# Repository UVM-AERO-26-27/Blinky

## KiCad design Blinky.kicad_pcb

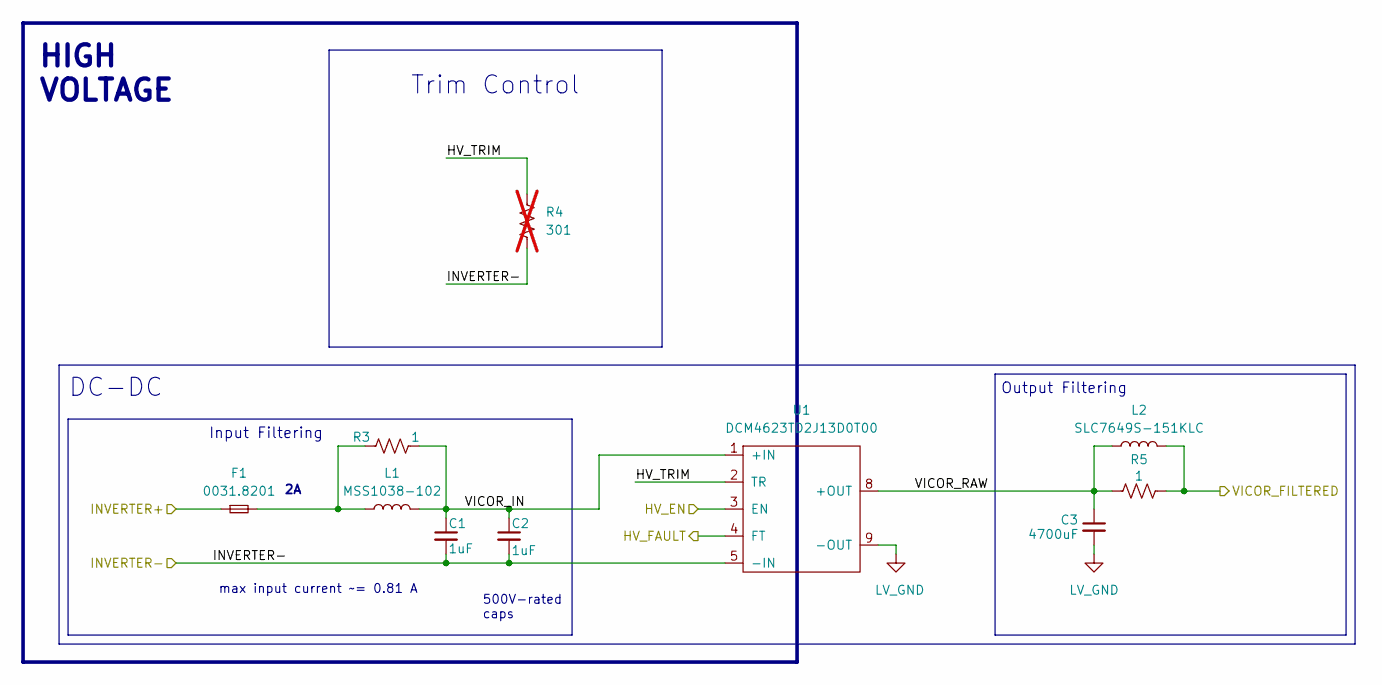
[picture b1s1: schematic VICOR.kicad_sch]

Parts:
C1, C2: 1uF; C_Rect_L18.0mm_W8.0mm_P15.00mm_FKS3_FKP3
C3: 4700uF; C_Radial_D12.5mm_H25.0mm_P5.00mm
F1: 0031.8201; Fuseholder_Cylinder-5x20mm_Schurter_0031_8201_Horizontal_Op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
L1: MSS1038-102
L2: SLC7649S-151KLC
R3, R5: 1; R_2512_6332Metric_Pad1.40x3.35mm_HandSolder; Manufacturer_Part_Number RK73H1JTTD1002F; Digikey part number 2019-RK73H1JTTD1002FCT-ND
R4: 301; R_0805_2012Metric_Pad1.20x1.40mm_HandSolder; not fitted
U1: DCM4623TD2J13D0T00

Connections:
/Control Signals/HV_EN: U1.3 (EN); also elsewhere on the board
/Control Signals/HV_FAULT: U1.4 (FT); also elsewhere on the board
/Control Signals/INVERTER-: C1.2, C2.2, R4.2, U1.5 (-IN); also elsewhere on the board
/GLV Connectors/VICOR_FILTERED: L2.2, R5.1; also elsewhere on the board
/TSV Connectors/INVERTER+: F1.1; also elsewhere on the board
/VICOR-1/HV_TRIM: R4.1, U1.2 (TR)
/VICOR-1/VICOR_IN: C1.1, C2.1, L1.2, R3.1, U1.1 (+IN)
/VICOR-1/VICOR_RAW: C3.1, L2.1, R5.2, U1.8 (+OUT)
LV_GND: C3.2, U1.9 (-OUT); also elsewhere on the board
unnamed: F1.2, L1.1, R3.2

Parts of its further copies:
C4, C5: 1uF; C_Rect_L18.0mm_W8.0mm_P15.00mm_FKS3_FKP3
C6: 4700uF; C_Radial_D12.5mm_H25.0mm_P5.00mm
L3: MSS1038-102
L4: SLC7649S-151KLC
R6, R8: 1; R_2512_6332Metric_Pad1.40x3.35mm_HandSolder; Manufacturer_Part_Number RK73H1JTTD1002F; Digikey part number 2019-RK73H1JTTD1002FCT-ND
R7: 301; R_0805_2012Metric_Pad1.20x1.40mm_HandSolder; not fitted
U2: DCM4623TD2J13D0T00

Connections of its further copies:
/Control Signals/HV_EN: U2.3 (EN); also elsewhere on the board
/Control Signals/HV_FAULT: U2.4 (FT); also elsewhere on the board
/Control Signals/INVERTER-: C4.2, C5.2, R7.2, U2.5 (-IN); also elsewhere on the board
/GLV Connectors/VICOR_FILTERED: L4.2, R8.1; also elsewhere on the board
/VICOR-2/HV_TRIM: R7.1, U2.2 (TR)
/VICOR-2/VICOR_IN: C4.1, C5.1, L3.2, R6.1, U2.1 (+IN)
/VICOR-2/VICOR_RAW: C6.1, L4.1, R8.2, U2.8 (+OUT)
LV_GND: C6.2, U2.9 (-OUT); also elsewhere on the board
unnamed 22: L3.1, R6.2; also elsewhere on the board

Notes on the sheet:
DC-DC
Input Filtering
Output Filtering
Trim Control
max input current ~= 0.81 A
HIGH VOLTAGE
500V-rated caps

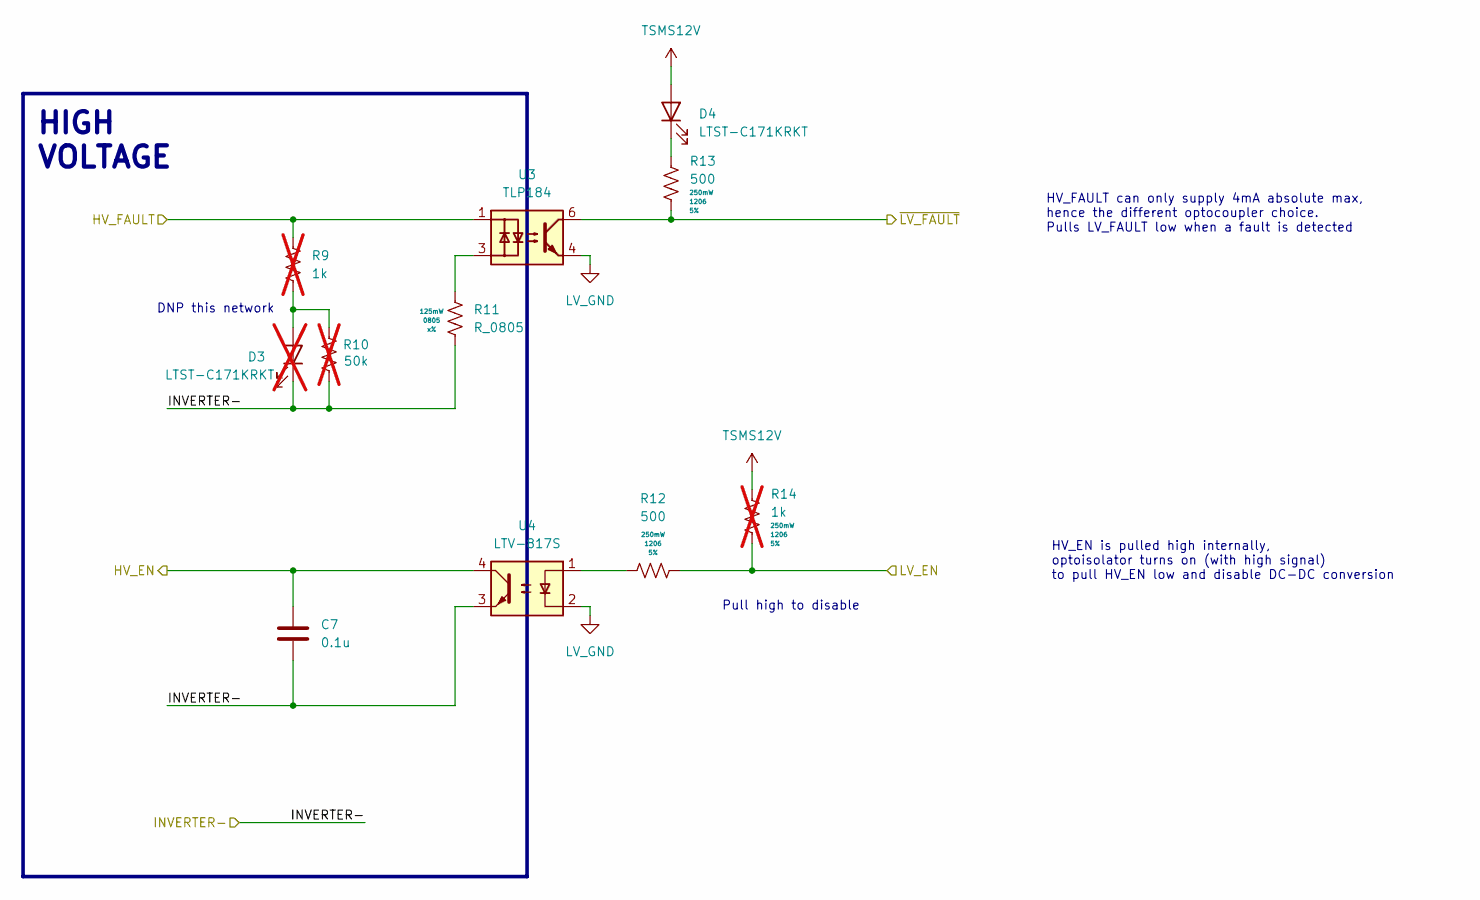
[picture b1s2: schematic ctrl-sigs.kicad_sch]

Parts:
C7: 0.1u; C_0603_1608Metric
D3: LTST-C171KRKT; LED_0805_2012Metric; not fitted
D4: LTST-C171KRKT; LED_0805_2012Metric
R9: 1k; R_0603_1608Metric_Pad0.98x0.95mm_HandSolder; not fitted
R10: 50k; R_0603_1608Metric_Pad0.98x0.95mm_HandSolder; Manufacturer_Part_Number RMCF0603FT1K00; Digikey part number RMCF0603FT1K00CT-ND; not fitted
R11: R_0805; R_0805_2012Metric_Pad1.20x1.40mm_HandSolder; Tolerance x%
R12, R13: 500; R_1206_3216Metric_Pad1.30x1.75mm_HandSolder; Tolerance 5%
R14: 1k; R_1206_3216Metric_Pad1.30x1.75mm_HandSolder; Tolerance 5%; not fitted
U3: TLP184; Toshiba_SOIC-4-6_4.4x3.6mm_P1.27mm
U4: LTV-817S; SMDIP-4_W9.53mm

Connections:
/Control Signals/HV_EN: C7.1, U4.4; also elsewhere on the board
/Control Signals/HV_FAULT: R9.1, U3.1; also elsewhere on the board
/Control Signals/INVERTER-: C7.2, D3.1 (K), R10.1, R11.2, U4.3; also elsewhere on the board
/Control Signals/LV_EN: R12.2, R14.1; also elsewhere on the board
/Control Signals/~LV_FAULT: R13.1, U3.6; also elsewhere on the board
LV_GND: U3.4, U4.2; also elsewhere on the board
unnamed: D3.2 (A), R9.2, R10.2
unnamed: D4.1 (K), R13.2
unnamed: R11.1, U3.3
unnamed: R12.1, U4.1
TSMS12V: D4.2 (A), R14.2; also elsewhere on the board

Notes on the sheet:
HV_FAULT can only supply 4mA absolute max, hence the different optocoupler choice. Pulls LV_FAULT low when a fault is detected
DNP this network
HV_EN is pulled high internally, optoisolator turns on (with high signal) to pull HV_EN low and disable DC-DC conversion
Pull high to disable
HIGH VOLTAGE

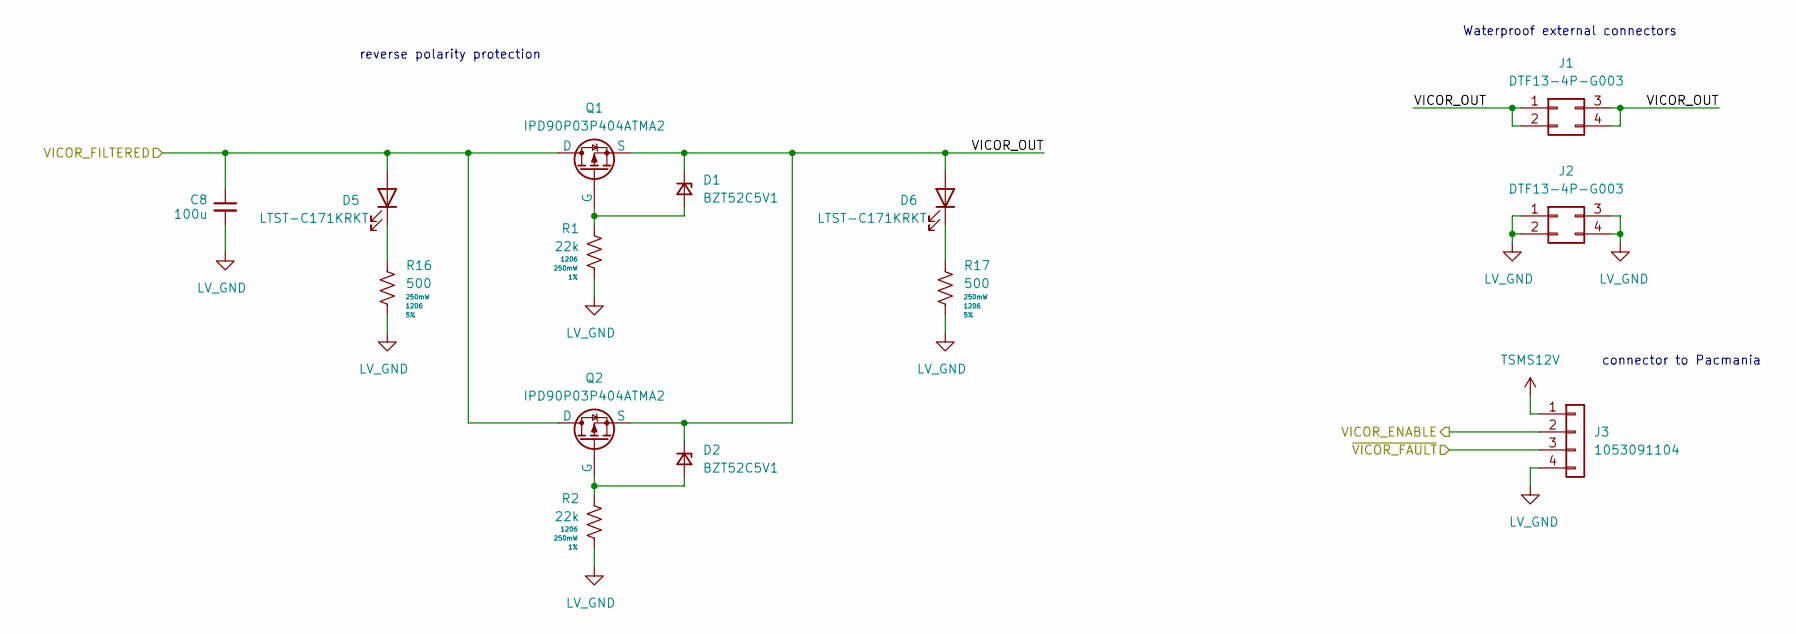
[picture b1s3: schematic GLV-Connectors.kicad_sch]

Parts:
C8: 100u; C_Radial_D12.5mm_H25.0mm_P5.00mm
D1, D2: BZT52C5V1; D_SOD-123F
D5, D6: LTST-C171KRKT; LED_0805_2012Metric
J1, J2: DTF13-4P-G003
J3: 1053091104
Q1, Q2: IPD90P03P404ATMA2
R1, R2: 22k; R_1206_3216Metric_Pad1.30x1.75mm_HandSolder; Tolerance 1%
R16, R17: 500; R_1206_3216Metric_Pad1.30x1.75mm_HandSolder; Tolerance 5%

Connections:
/Control Signals/LV_EN: J3.2; also elsewhere on the board
/Control Signals/~LV_FAULT: J3.3; also elsewhere on the board
/GLV Connectors/VICOR_FILTERED: C8.1, D5.2 (A), Q1.1 (D), Q2.1 (D); also elsewhere on the board
/GLV Connectors/VICOR_OUT: D1.1 (K), D2.1 (K), D6.2 (A), J1.1, J1.2, J1.3, J1.4, Q1.3 (S), Q2.3 (S)
LV_GND: C8.2, J2.1, J2.2, J2.3, J2.4, J3.4, R1.1, R2.1, R16.1, R17.1; also elsewhere on the board
unnamed: D1.2 (A), Q1.2 (G), R1.2
unnamed: D2.2 (A), Q2.2 (G), R2.2
unnamed: D5.1 (K), R16.2
unnamed: D6.1 (K), R17.2
TSMS12V: J3.1; also elsewhere on the board

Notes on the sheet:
reverse polarity protection
Waterproof external connectors
connector to Pacmania

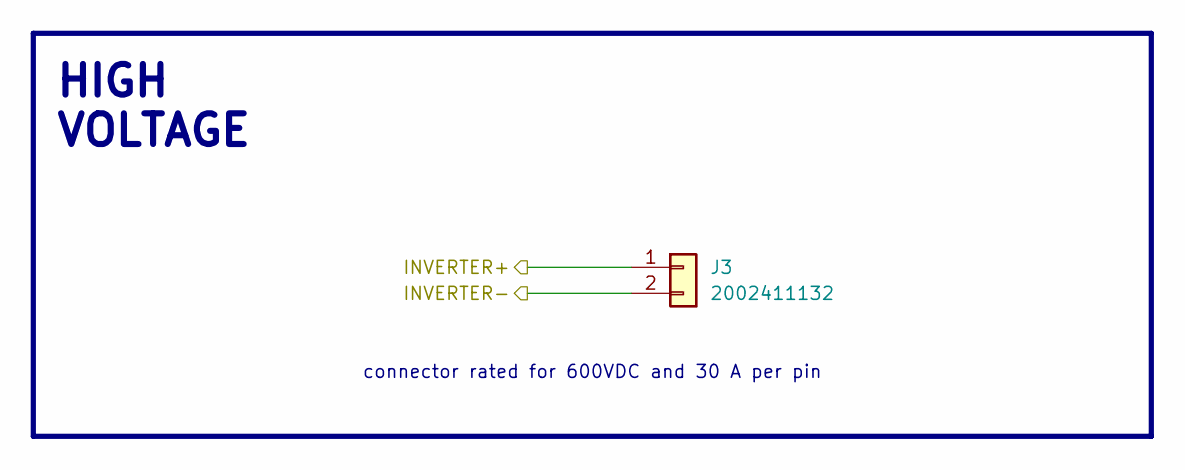
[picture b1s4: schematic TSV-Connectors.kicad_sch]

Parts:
J3: 2002411132

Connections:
/Control Signals/LV_EN: J3.2; also elsewhere on the board
TSMS12V: J3.1; also elsewhere on the board

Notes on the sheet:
connector rated for 600VDC and 30 A per pin
HIGH VOLTAGE

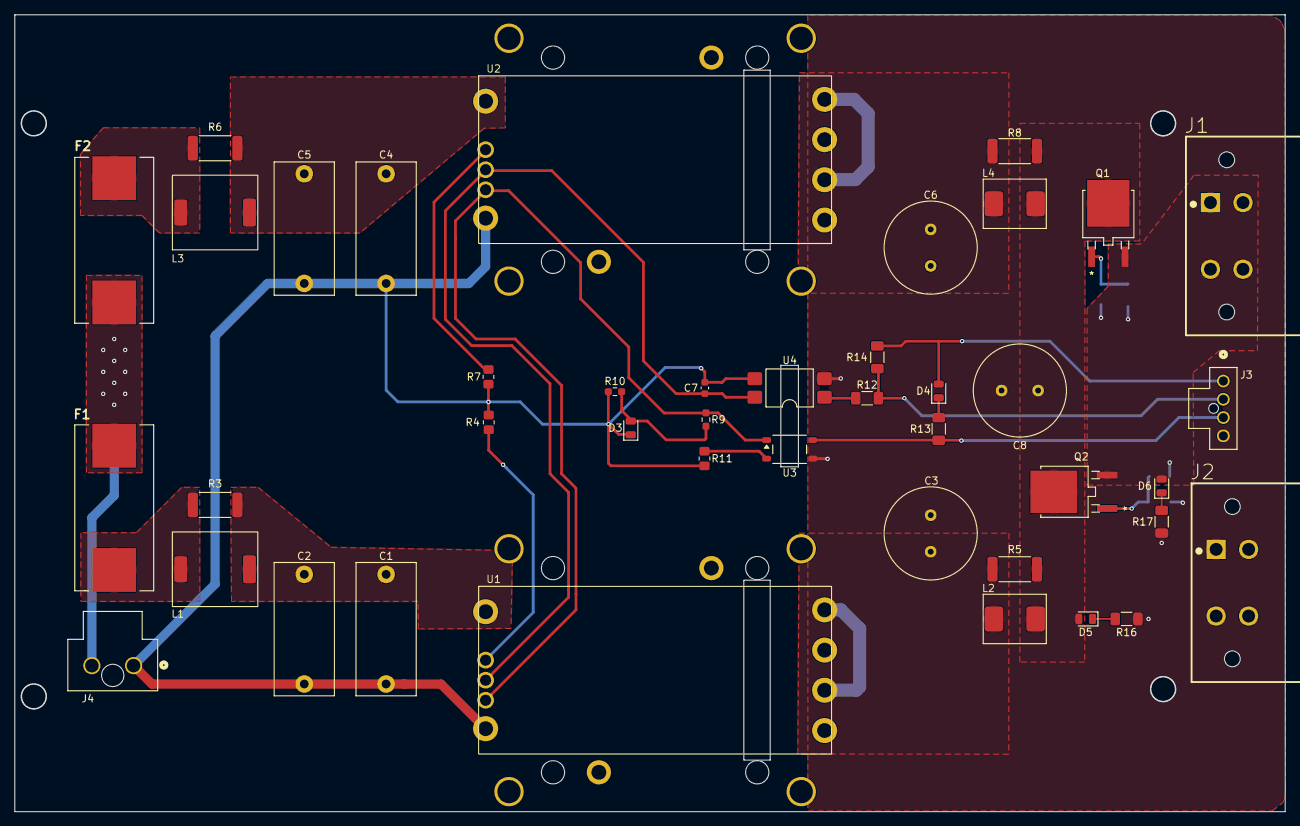
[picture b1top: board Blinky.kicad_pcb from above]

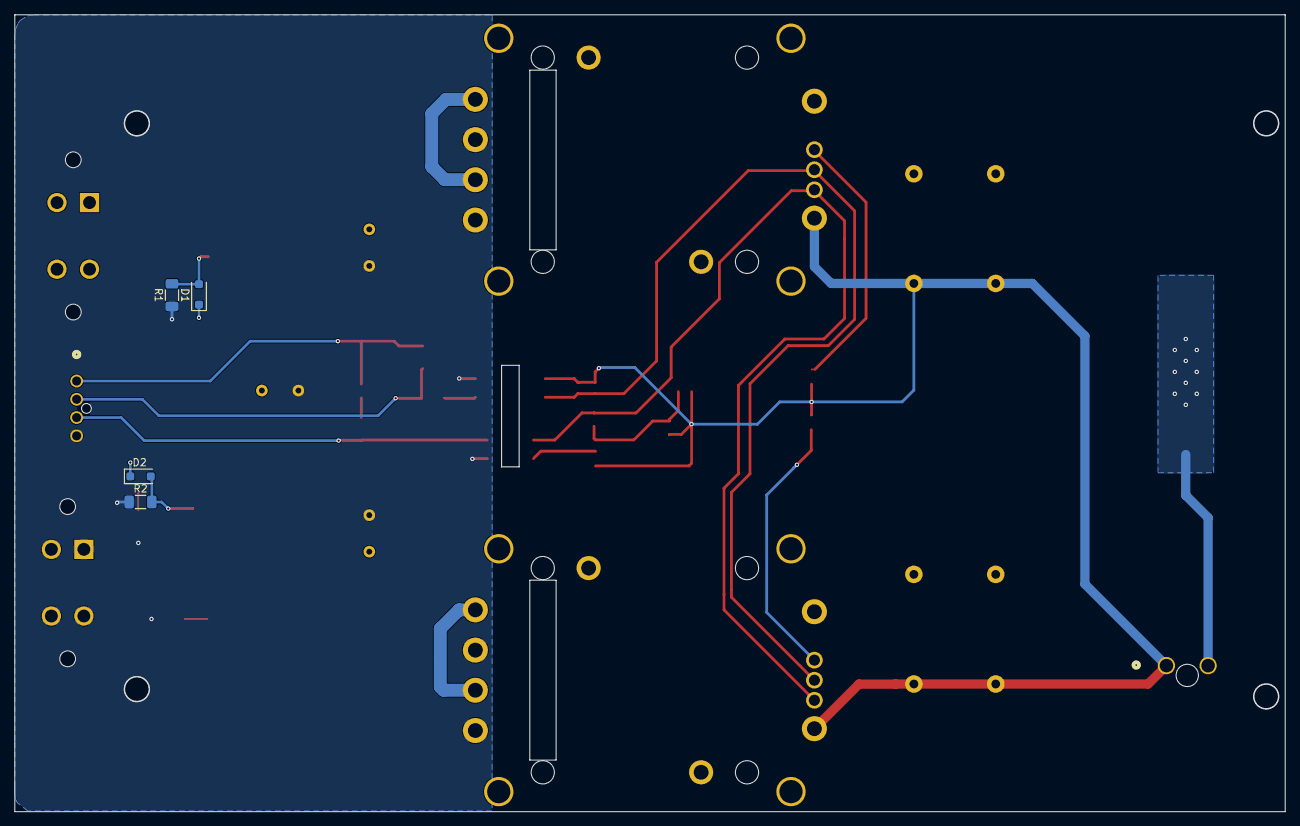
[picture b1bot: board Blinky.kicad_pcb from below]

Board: 4 copper layers, 173.8 x 109.0 mm, 46 parts (4 on the bottom side), 26 nets.

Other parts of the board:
F2: 0031.8221; Schurter 0031.8221
J4: 2002411132

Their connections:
/Control Signals/INVERTER-: J4.1; also elsewhere on the board
/TSV Connectors/INVERTER+: F2.1, J4.2; also elsewhere on the board
unnamed 22: F2.2; also elsewhere on the board
